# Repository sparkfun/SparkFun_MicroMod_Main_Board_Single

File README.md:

SparkFun MicroMod Main Board - Single
========================================

[*SparkFun MicroMod Main Board - Single (DEV-20748)*](https://www.sparkfun.com/products/20748)

The MicroMod Main Board - Single is a specialized carrier board that allows you to interface a MicroMod Processor Board with a single MicroMod Function Board. With the M.2 MicroMod connector, connecting your Processor and Function Boards is a breeze. Simply match up the key on your board's beveled edge connector to the key on the M.2 connector and secure the boards with screws.

The Single Main Board includes one USB-C connector for power and programming the Processor Board. A jumper is available on the back of the board to isolate the USB C's shield pin. Two buttons for reset and boot are also populated on the board. Processor Board pins are also broken out as 2x5 SWD pins. Also, included on the board is a 2A resettable fuse and 3.3V/1A voltage regulator. A second 3.3V/500mA voltage regulator is included on the board to power your Qwiic-enabled devices. We've even added convenient PTH jumpers for advanced users looking to bypass the fuse and measure the current consumption on the 5V and 3.3V lines for low-power testing. For those that need to go remote with their application, the board includes a 2-pin JST connector and a single-cell LiPo MCP73831 charge IC (set to a charge rate of 500mA).

Four status LEDs are available for power and charging. These can also be disabled through jumpers. There is a microSD card socket so you can also plug in a microSD card for data logging. The microSD socket can be disabled through the I/O pins. Finally, two Qwiic connectors are populated on the board with built-in pull-up resistors to easily add Qwiic-enabled I<sup>2</sup>C devices to your projects!

Repository Contents
-------------------

* **/Firmware** - Arduino example code from the tutorial
* **/Hardware** - Eagle design files (.brd, .sch)
* **/Production** - Production panel files (.brd)

Documentation
--------------

* **[Hookup Guide V2](https://learn.sparkfun.com/tutorials/2683)** - Basic hookup guide

Product Versions
----------------
* [DEV-20748](https://www.sparkfun.com/products/20748) - v2.1
* [DEV-18632](https://www.sparkfun.com/products/18575)- Initial release, v1.1

Version History
---------------
* v2.1
* v1.1 - Initial Release

License Information
-------------------

This product is _**open source**_! 

Please review the LICENSE.md file for license information. 

If you have any questions or concerns on licensing, please contact technical support on our [SparkFun forums](https://forum.sparkfun.com/viewforum.php?f=152).

Distributed as-is; no warranty is given.

- Your friends at SparkFun.

_<COLLABORATION CREDIT>_

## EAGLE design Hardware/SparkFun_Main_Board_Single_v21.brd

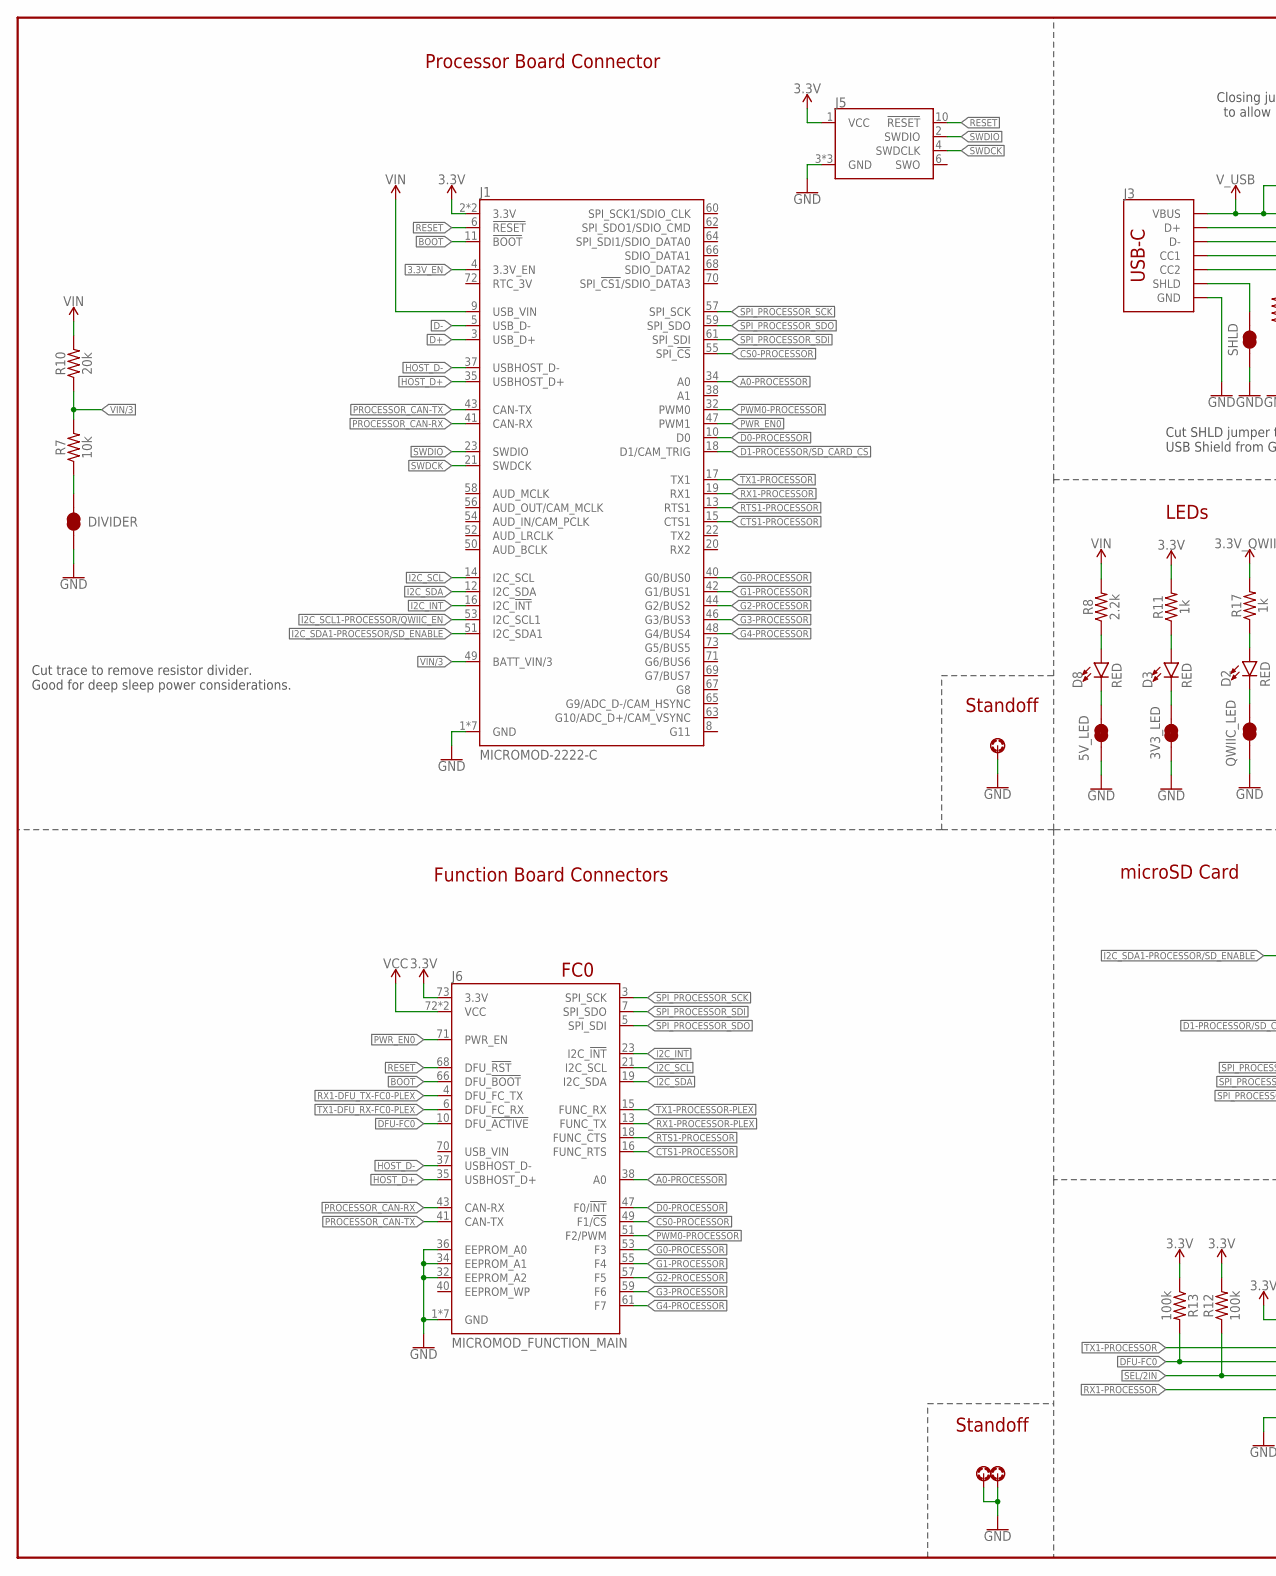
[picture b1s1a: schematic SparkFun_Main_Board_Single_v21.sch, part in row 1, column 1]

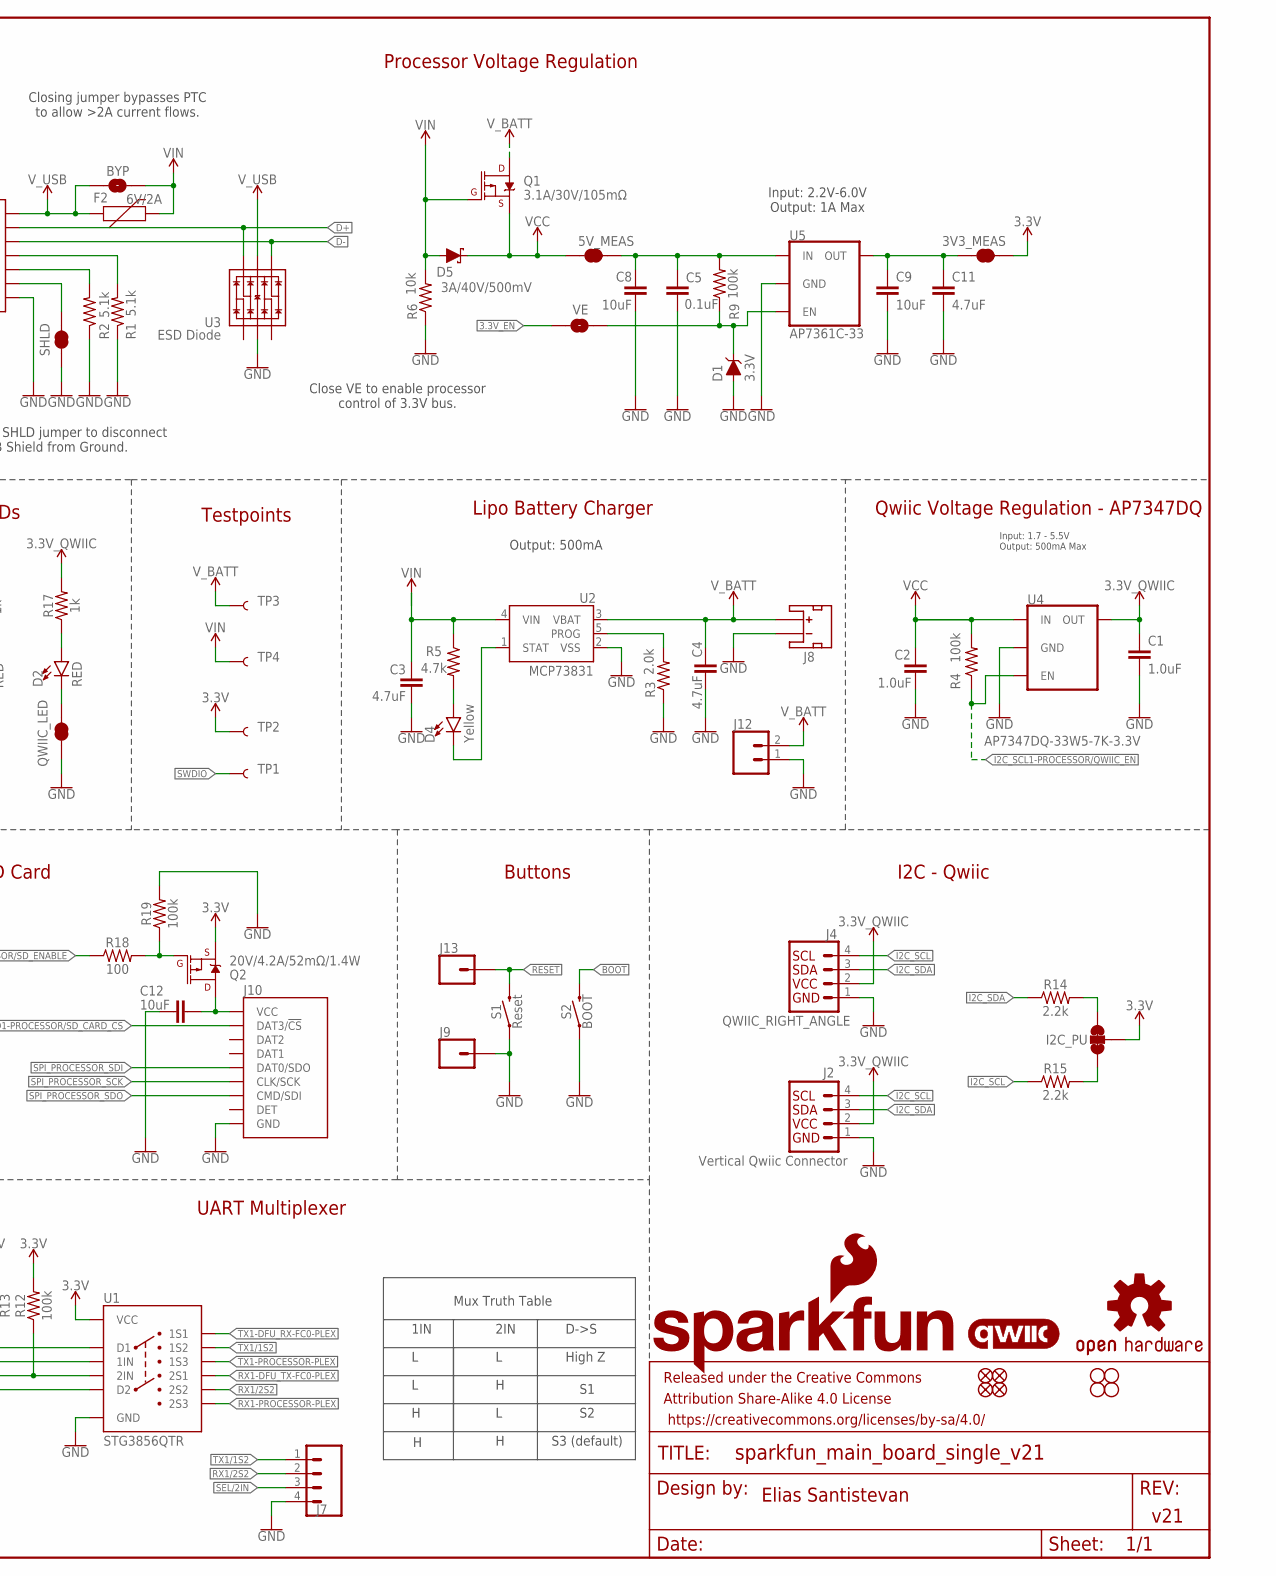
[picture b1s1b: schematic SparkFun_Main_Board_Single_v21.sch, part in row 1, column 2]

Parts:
3V3_LED, 5V_LED: JUMPER-SMT_2_NC_TRACE_SILK; SMT-JUMPER_2_NC_TRACE_SILK
3V3_MEAS, 5V_MEAS: JUMPER-COMBO_2_NC_TRACE; COMBO-JUMPER_2_NC_TRACE
BYP: JUMPER-SMT_2_NO_SILK; SMT-JUMPER_2_NO_SILK
C1, C2: 1.0uF; 0603
C3, C4, C11: 4.7uF; 0603
C5: 0.1uF; 0603
C8: 10uF; 0805
C9, C12: 10uF; 0603
D1: 3.3V; SOD-323
D2, D3, D8: RED; LED-0603
D4: Yellow; LED-0603
D5: 3A/40V/500mV; SMA-DIODE
DIVIDER: JUMPER-SMT_2_NC_TRACE_SILK; SMT-JUMPER_2_NC_TRACE_SILK
F2: 6V/2A; 1210
FD1, FD2, FD3, FD4: FIDUCIAL1X2; FIDUCIAL-1X2
FRAME1: FRAME-LEDGER; CREATIVE_COMMONS
H2, H4, H8: STAND-OFF-REFLOW-M2.5_2.5MM_TALL; STAND-OFF-REFLOW-M2.5
H14, H15, H16, H17: STAND-OFFTIGHT; STAND-OFF-TIGHT
I2C_PU: JUMPER-SMT_3_2-NC_TRACE_SILK; SMT-JUMPER_3_2-NC_TRACE_SILK
J1: MICROMOD-2222-C; M.2-CONNECTOR-E
J2: Vertical Qwiic Connector; JST04_1MM_VERT
J3: USB_C_2-LAYER_PADS; USB-C-16P-2LAYER-PADS
J4: QWIIC_RIGHT_ANGLE; JST04_1MM_RA
J5: CORTEX_JTAG_DEBUG_MINIMUM_PTH; 2X5-PTH-1.27MM
J6: MICROMOD_FUNCTION_MAIN; M.2-CONNECTOR-E-FUNCTION-STANDARD
J7: CONN_041X04_NO_SILK; 1X04_NO_SILK
J8: JST_2MM_MALE; JST-2-SMD
J9, J13: CONN_01PTH_NO_SILK_YES_STOP; 1X01_NO_SILK
J10: MICRO-SD-PUSH-PUSH-EXT-PIN; MICROSD-EXTERNALPIN
J12: CONN_021X02_NO_SILK; 1X02_NO_SILK
LOGO1: QWIIC_LOGO_8MM; QWIIC_8MM
LOGO2: SFE_LOGO_NAME_FLAME.3_INCH; SFE_LOGO_NAME_FLAME_.3
LOGO3: OSHW-LOGOL; OSHW-LOGO-L
Q1: 3.1A/30V/105mΩ; SOT23-3
Q2: 20V/4.2A/52mΩ/1.4W; SOT23-3
QWIIC_LED: JUMPER-SMT_2_NC_TRACE_SILK; SMT-JUMPER_2_NC_TRACE_SILK
R1, R2: 5.1k; 0603
R3: 2.0k; 0603
R4, R9, R12, R13, R19: 100k; 0603
R5: 4.7k; 0603
R6, R7: 10k; 0603
R8, R14, R15: 2.2k; 0603
R10: 20k; 0603
R11, R17: 1k; 0603
R18: 100; 0603
S1: Reset; TACTILE_SWITCH_SMD_5.2MM
S2: BOOT; TACTILE_SWITCH_SMD_5.2MM
SHLD: JUMPER-SMT_2_NC_TRACE_SILK; SMT-JUMPER_2_NC_TRACE_SILK
TP1, TP2, TP3, TP4: TEST-POINT3X5; PAD.03X.05
U1: STG3856QTR; STG3856
U2: MCP73831; SOT23-5
U3: ESD Diode; SOT-23-6
U4: AP7347DQ-33W5-7K-3.3V; SOT25
U5: AP7361C-33; UDFN-8
VE: JUMPER-SMT_2_NO_SILK; SMT-JUMPER_2_NO_SILK

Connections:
3.3V: 3V3_MEAS.2, 3V3_MEAS.4 (2), I2C_PU.2, J1.2 (3.3V), J1.74 (3.3V), J5.1 (VCC), J6.73 (3.3V), Q2.2 (S), R11.2, R12.2, R13.1, TP2.1, U1.P11 (VCC)
3.3V_EN: J1.4 (3.3V_EN), VE.1
3.3V_EN_VE: D1.C, R9.1, U5.5 (EN), VE.2
3.3V_QWIIC: C1.1, J2.2, J4.2, R17.2, U4.5 (OUT)
3V3_MEAS: 3V3_MEAS.1, 3V3_MEAS.3 (1), C9.1, C11.1, U5.1 (OUT)
!BOOT!: J1.11 (!BOOT!), J6.66 (DFU_!BOOT!), S2.3 (2), S2.4 (2)
!CS0!-PROCESSOR: J1.55 (SPI_!CS!), J6.49 (F1/!CS!)
!DFU-FC0!: J6.10 (DFU_!ACTIVE!), R13.2, U1.P12 (1IN)
!RESET!: J1.6 (!RESET!), J5.10 (!RESET), J6.68 (DFU_!RST!), J13.1, S1.3 (2), S1.4 (2)
!SEL!/2IN: J7.3, R12.1, U1.P10 (2IN)
A0-PROCESSOR: J1.34 (A0), J6.38 (A0)
CTS1-PROCESSOR: J1.15 (CTS1), J6.16 (FUNC_RTS)
D0-PROCESSOR: J1.10 (D0), J6.47 (F0/!INT!)
D1-PROCESSOR/SD_CARD_!CS!: J1.18 (D1/CAM_TRIG), J10.2 (DAT3/!CS!)
D+: J1.3 (USB_D+), J3.A6 (D+), J3.B6 (D+), U3.6 (IO4)
D-: J1.5 (USB_D-), J3.A7 (D-), J3.B7 (D-), U3.4 (IO3)
G0-PROCESSOR: J1.40 (G0/BUS0), J6.53 (F3)
G1-PROCESSOR: J1.42 (G1/BUS1), J6.55 (F4)
G2-PROCESSOR: J1.44 (G2/BUS2), J6.57 (F5)
G3-PROCESSOR: J1.46 (G3/BUS3), J6.59 (F6)
G4-PROCESSOR: J1.48 (G4/BUS4), J6.61 (F7)
GND: 3V3_LED.1, 5V_LED.1, C1.2, C2.2, C3.2, C4.2, C5.2, C8.2, C9.2, C11.2, C12.2, D1.A, DIVIDER.1, H2.1, H4.1, H8.1, J1.1 (GND), J1.7 (GND), J1.33 (GND), J1.36 (GND), J1.39 (GND), J1.45 (GND), J1.75 (GND), J2.1, J3.GND, J3.GND2 (GND), J4.1, J5.3 (GND), J5.5 (GND), J5.9 (GND), J6.1 (GND), J6.2 (GND), J6.8 (GND), J6.32 (EEPROM_A2), J6.33 (GND), J6.34 (EEPROM_A1), J6.36 (EEPROM_A0), J6.39 (GND), J6.45 (GND), J6.75 (GND), J7.4, J8.1 (-), J9.1, J10.6 (GND), J10.10 (GND), J10.11 (GND), J10.12 (GND), J10.13 (GND), J12.1, QWIIC_LED.1, R1.1, R2.1, R3.1, R6.1, R19.2, S1.1, S1.2 (1), S2.1, S2.2 (1), SHLD.1, U1.P5 (GND), U2.2 (VSS), U3.2 (VSS), U4.2 (GND), U5.4 (GND), U5.EP (GND)
HOST_D+: J1.35 (USBHOST_D+), J6.35 (USBHOST_D+)
HOST_D-: J1.37 (USBHOST_D-), J6.37 (USBHOST_D-)
I2C_!INT!: J1.16 (I2C_!INT!), J6.23 (I2C_!INT!)
I2C_SCL: J1.14 (I2C_SCL), J2.4, J4.4, J6.21 (I2C_SCL), R15.1
I2C_SCL1-PROCESSOR/QWIIC_EN: J1.53 (I2C_SCL1), R4.1, U4.3 (EN)
I2C_SDA: J1.12 (I2C_SDA), J2.3, J4.3, J6.19 (I2C_SDA), R14.1
I2C_SDA1-PROCESSOR/!SD_ENABLE!: J1.51 (I2C_SDA1), R18.1
unnamed: 5V_LED.2, D8.C
unnamed: D3.A, R11.1
unnamed: J3.B5 (CC2), R2.2
unnamed: J3.A5 (CC1), R1.2
unnamed: R3.2, U2.5 (PROG)
unnamed: DIVIDER.2, R7.1
unnamed: D4.C, U2.1 (STAT)
unnamed: D4.A, R5.2
unnamed: 3V3_LED.2, D3.C
unnamed: I2C_PU.3, R14.2
unnamed: D8.A, R8.1
unnamed: I2C_PU.1, R15.2
unnamed: D2.A, R17.1
unnamed: D2.C, QWIIC_LED.2
unnamed: C12.1, J10.4 (VCC), Q2.3 (D)
unnamed: Q2.1 (G), R18.2, R19.1
PROCESSOR_CAN-RX: J1.41 (CAN-RX), J6.43 (CAN-RX)
PROCESSOR_CAN-TX: J1.43 (CAN-TX), J6.41 (CAN-TX)
PWM0-PROCESSOR: J1.32 (PWM0), J6.51 (F2/PWM)
PWR_EN0: J1.47 (PWM1), J6.71 (PWR_EN)
RTS1-PROCESSOR: J1.13 (RTS1), J6.18 (FUNC_CTS)
RX1-DFU_TX-FC0-PLEX: J6.4 (DFU_FC_TX), U1.P9 (2S1)
RX1-PROCESSOR: J1.19 (RX1), U1.P6 (D2)
RX1-PROCESSOR-PLEX: J6.13 (FUNC_TX), U1.P7 (2S3)
RX1/2S2: J7.2, U1.P8 (2S2)
SHLD: J3.SHLD1 (SHLD), J3.SHLD2 (SHLD), J3.SHLD3 (SHLD), J3.SHLD4 (SHLD), SHLD.2
SPI_PROCESSOR_SCK: J1.57 (SPI_SCK), J6.3 (SPI_SCK), J10.5 (CLK/SCK)
SPI_PROCESSOR_SDI: J1.61 (SPI_SDI), J6.7 (SPI_SDO), J10.7 (DAT0/SDO)
SPI_PROCESSOR_SDO: J1.59 (SPI_SDO), J6.5 (SPI_SDI), J10.3 (CMD/SDI)
SWDCK: J1.21 (SWDCK), J5.4 (SWDCLK)
SWDIO: J1.23 (SWDIO), J5.2 (SWDIO), TP1.1
TX1-DFU_RX-FC0-PLEX: J6.6 (DFU_FC_RX), U1.P1 (1S1)
TX1-PROCESSOR: J1.17 (TX1), U1.P4 (D1)
TX1-PROCESSOR-PLEX: J6.15 (FUNC_RX), U1.P3 (1S3)
TX1/1S2: J7.1, U1.P2 (1S2)
VCC: 5V_MEAS.1, 5V_MEAS.3 (1), C2.1, D5.C, J6.72 (VCC), J6.74 (VCC), Q1.2 (S), R4.2, U4.1 (IN)
VCC_MEAS: 5V_MEAS.2, 5V_MEAS.4 (2), C5.1, C8.1, R9.2, U5.8 (IN)
VIN: BYP.2, C3.1, D5.A, F2.2, J1.9 (USB_VIN), Q1.1 (G), R5.1, R6.2, R8.2, R10.2, TP4.1, U2.4 (VIN)
VIN/3: J1.49 (BATT_VIN/3), R7.2, R10.1
V_BATT: C4.1, J8.2 (+), J12.2, Q1.3 (D), TP3.1, U2.3 (VBAT)
V_USB: BYP.1, F2.1, J3.VBUS1 (VBUS), J3.VBUS2 (VBUS), U3.5 (VCC)

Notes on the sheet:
Function Board Connectors
Processor Board Connector
v21
I2C - Qwiic
FC0
Lipo Battery Charger
Testpoints
Processor Voltage Regulation
Closing jumper bypasses PTC to allow >2A current flows.
Input: 2.2V-6.0V Output: 1A Max
Close VE to enable processor control of 3.3V bus.
LEDs
Buttons
Elias Santistevan
Standoff
Mux Truth Table
1IN
2IN
D->S
High Z
S3 (default)
UART Multiplexer
Qwiic Voltage Regulation - AP7347DQ
Input: 1.7 - 5.5V Output: 500mA Max
Output: 500mA
Cut SHLD jumper to disconnect USB Shield from Ground.
microSD Card
Cut trace to remove resistor divider. Good for deep sleep power considerations.

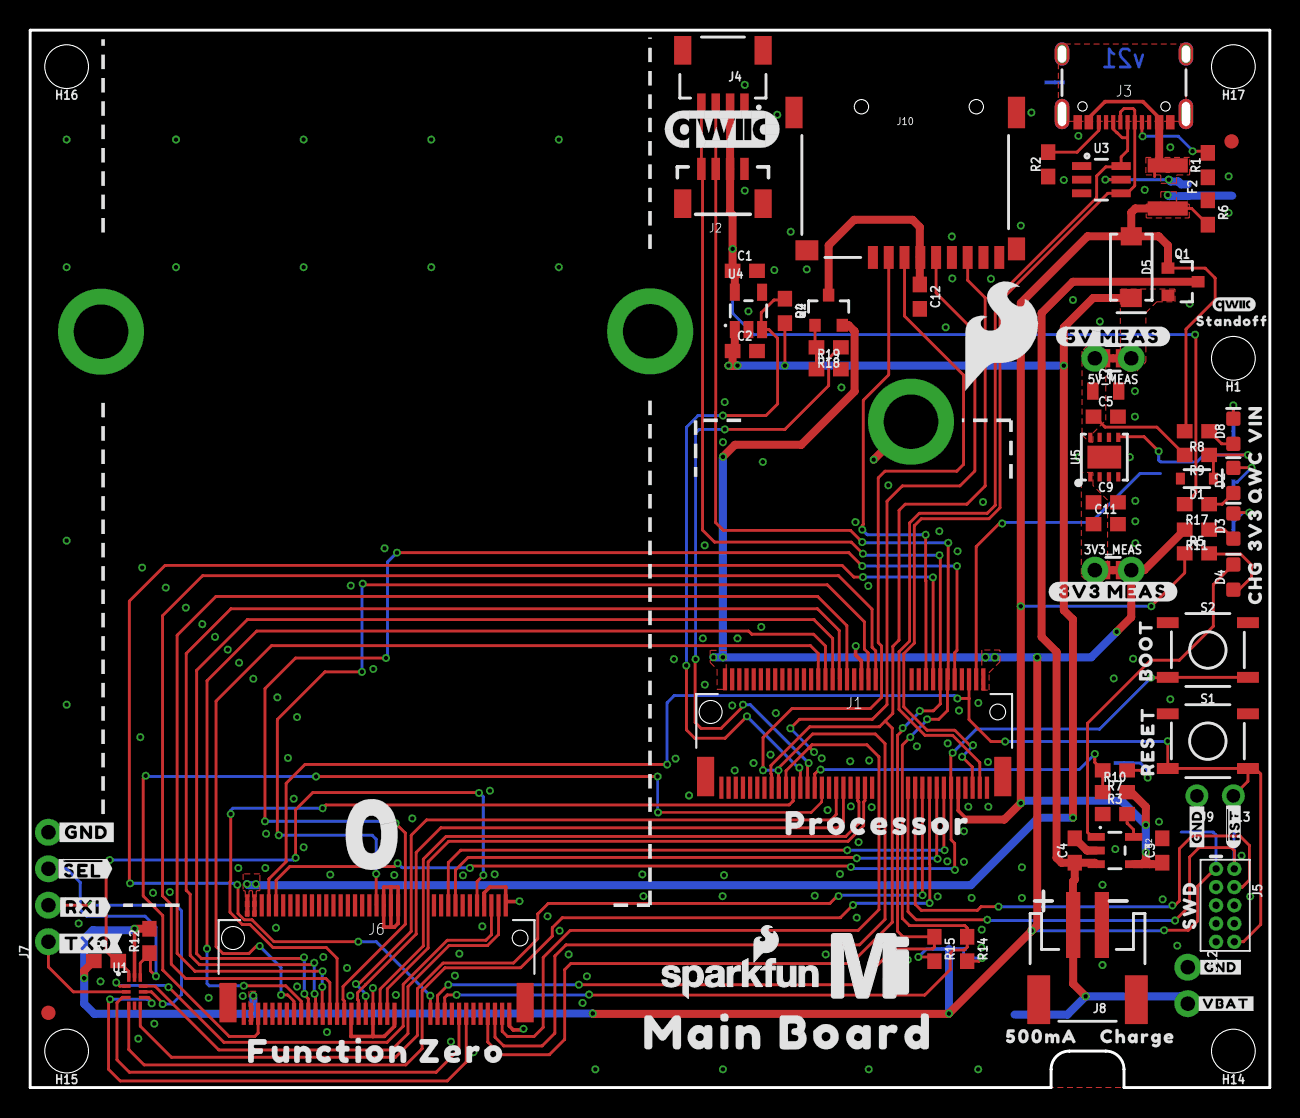
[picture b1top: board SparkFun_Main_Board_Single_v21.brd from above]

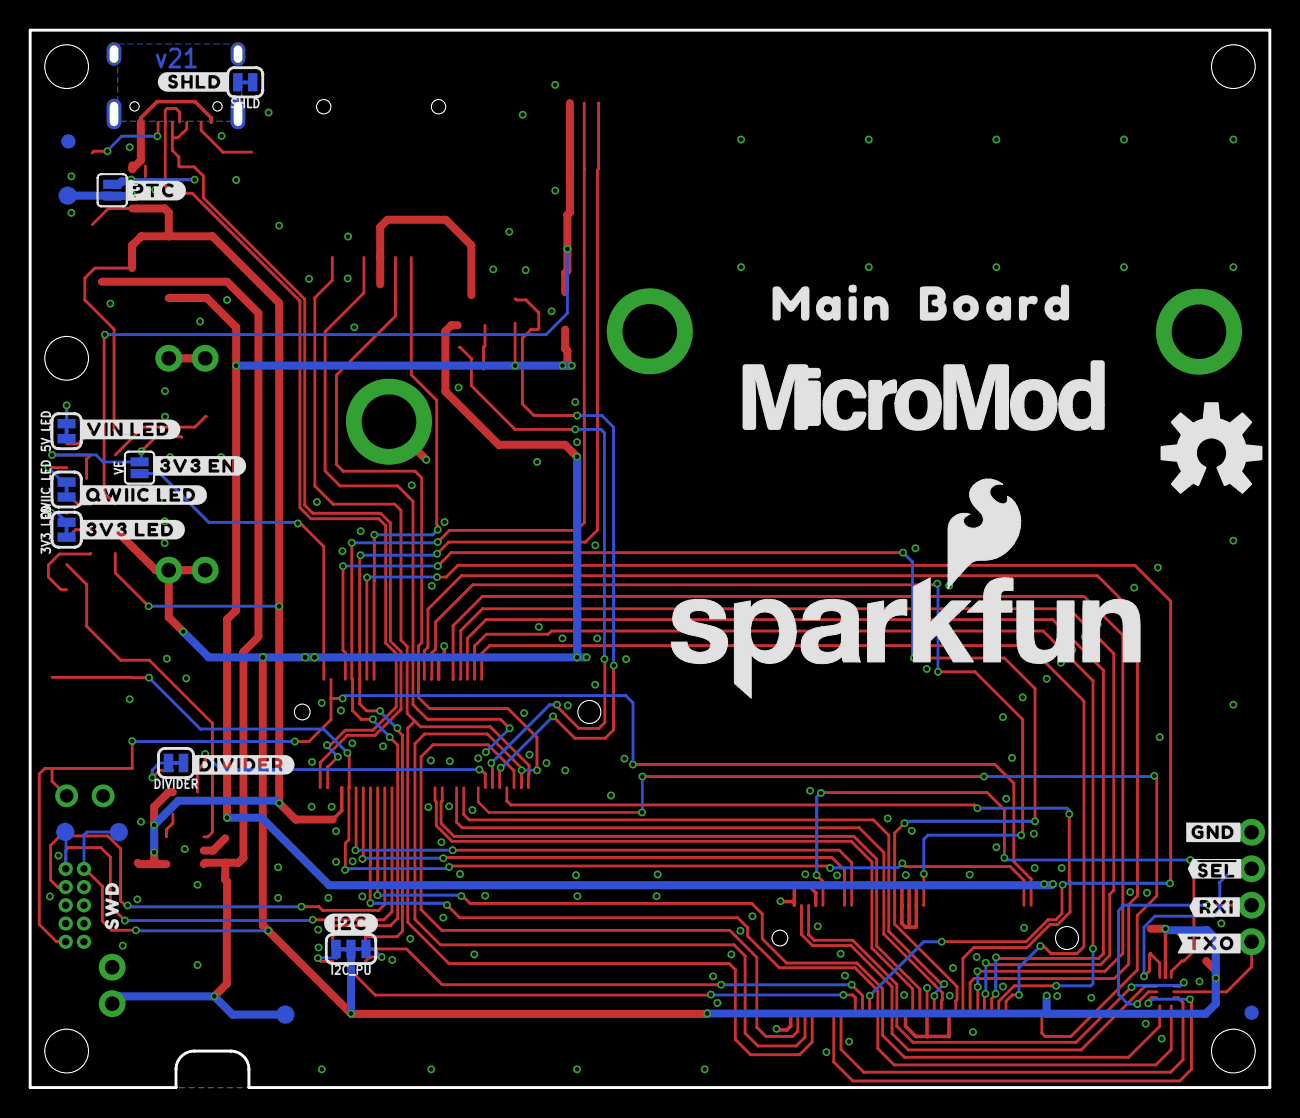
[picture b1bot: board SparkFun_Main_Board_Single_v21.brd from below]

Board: 2 copper layers, 86.4 x 73.7 mm, 130 parts (32 on the bottom side), 70 nets.

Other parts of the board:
FRAME2: FRAME-LEDGERNO_FOOTPRINT; DUMMY
H1: STAND-OFFTIGHT; STAND-OFF-TIGHT
U$1: #TXO#7
U$2: #RXI#6
U$3: #PTC#15
U$4: 3V332533
U$5: VIN32532
U$6: CHG32531
U$7: #SHLD#501
U$8: BOOT32541
U$9: RESET32540
U$10: PROCESSOR525
U$11: FUNCTION_ZERO520
U$12: ##SEL##5
U$13: MAIN523
U$14: MICROMOD_MI_LOGO_1
U$15: 0523
U$16, U$29: #GND#3
U$17: MICROMOD_LOGO_1
U$18: BOARD524
U$19: ##SEL##3
U$20: #RXI#4
U$21: MAIN_BOARD5523
U$22: QWIIC_3MM
U$23: STANDOFF501
U$24: SFE_LOGO_FLAME_.3
U$25, U$32: SWD6522
U$26: #3V3_MEAS#6522
U$27: CHARGE501
U$28: #TXO#5
U$30: #I2C#501
U$31: #5V_MEAS#6522
U$33: 500MA6520
U$34: SFE_LOGO_NAME_FLAME_.1
U$35: QWC4
U$36, U$37: #GND#10
U$38: ##RST##8
U$39: #VBAT#9
U$49: #3V3_EN#23
U$50: #3V3_LED#22
U$51: #QWIIC_LED#22
U$52: #DIVIDER#23
U$53: #VIN_LED#24

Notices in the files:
parts and their libraries:
SparkFun-Connectors: Licensing: Creative Commons ShareAlike 4.0 International - https://creativecommons.org/licenses/by-sa/4.0
SparkFun-Aesthetics: Released under the Creative Commons Attribution Share-Alike 4.0 License
SparkFun-Aesthetics: https://creativecommons.org/licenses/by-sa/4.0
